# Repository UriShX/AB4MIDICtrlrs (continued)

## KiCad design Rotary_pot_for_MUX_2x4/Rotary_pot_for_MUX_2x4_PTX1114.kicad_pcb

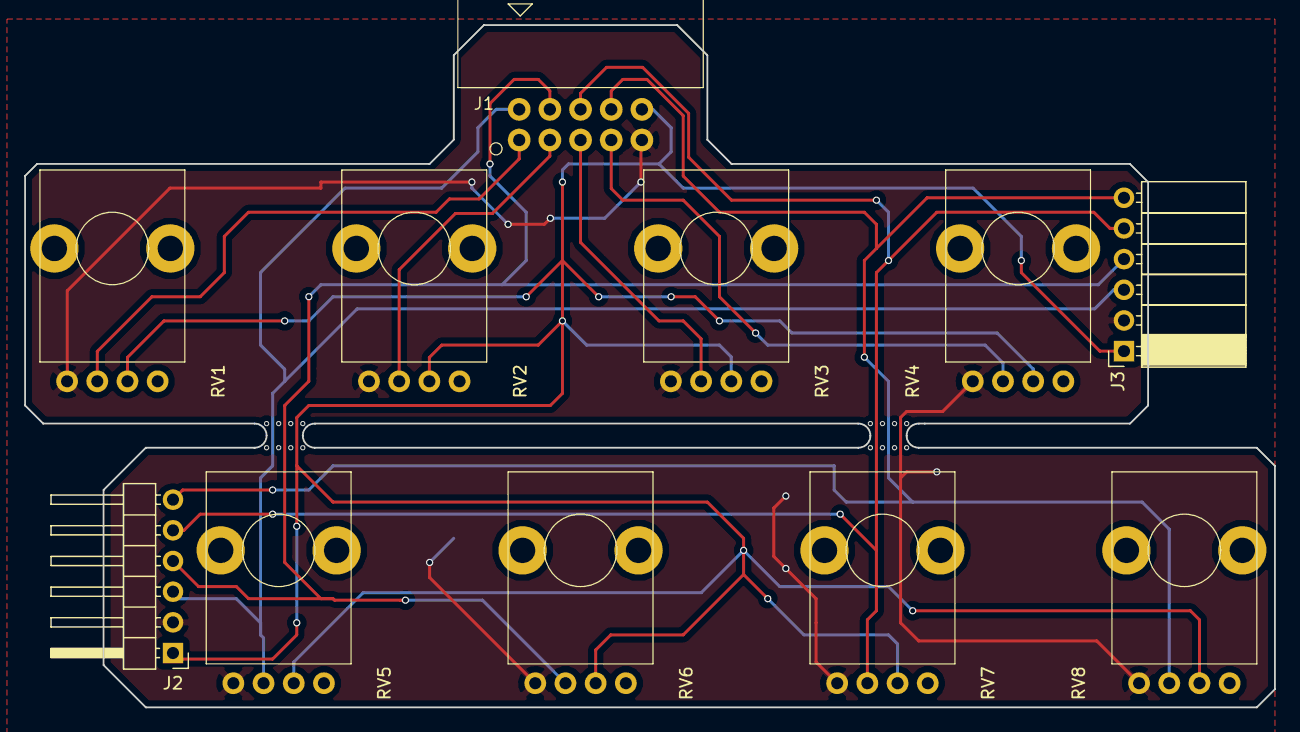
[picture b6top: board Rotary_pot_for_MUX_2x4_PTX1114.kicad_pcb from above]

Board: 2 copper layers, 103.5 x 56.5 mm, 11 parts (0 on the bottom side), 10 nets.

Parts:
J1: Conn_02x05_Odd_Even; 2X5-SHROUDED_rightAngle
J2: Conn_01x06_Male; Pin_Header_Angled_1x06_Pitch2.54mm
J3: Conn_01x06_Female; Socket_Strip_Angled_1x06_Pitch2.54mm
RV1, RV2, RV3, RV4, RV5, RV6, RV7, RV8: 10k_B; Potentiometer_Bourns_or_TT_PTV_PTT111-4_Horizontal

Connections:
GND: J1.9, J2.2, J3.2, RV1.1, RV2.1, RV3.1, RV4.1, RV5.1, RV6.1, RV7.1, RV8.1
unnamed: J1.1, RV1.2
unnamed: J1.2, J2.3, J3.3, RV5.2
unnamed: J1.3, RV2.2
unnamed: J1.4, J2.4, J3.4, RV6.2
unnamed: J1.5, RV3.2
unnamed: J1.6, J2.5, J3.5, RV7.2
unnamed: J1.7, RV4.2
unnamed: J1.8, J2.6, J3.6, RV8.2
VCC: J1.10, J2.1, J3.1, RV1.3, RV2.3, RV3.3, RV4.3, RV5.3, RV6.3, RV7.3, RV8.3

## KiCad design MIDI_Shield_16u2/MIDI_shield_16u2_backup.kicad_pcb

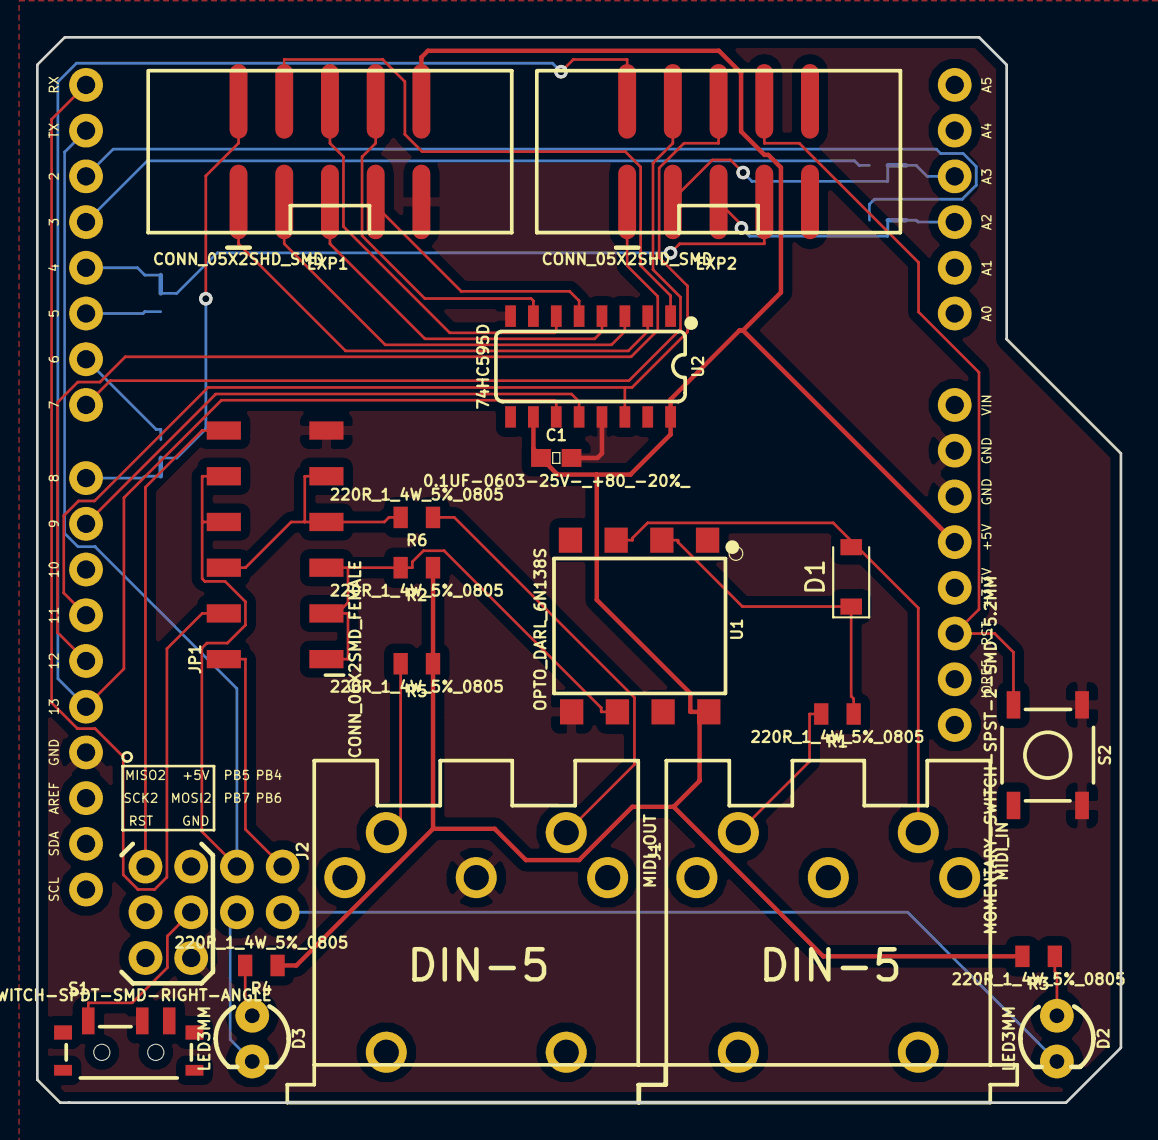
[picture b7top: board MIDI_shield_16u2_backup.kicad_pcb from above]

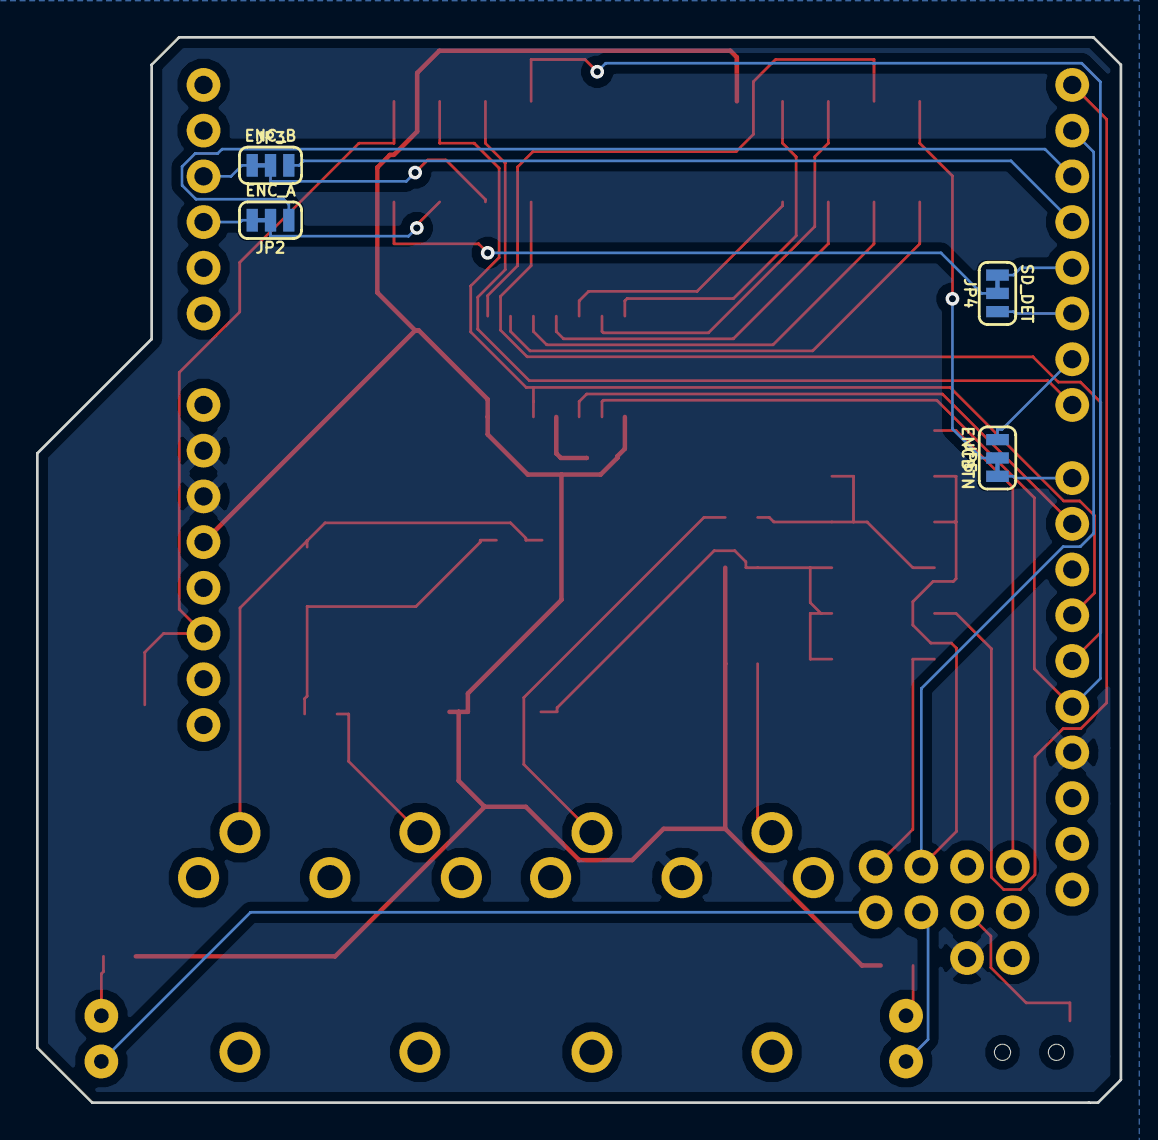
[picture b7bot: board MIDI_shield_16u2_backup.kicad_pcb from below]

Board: 2 copper layers, 60.2 x 59.2 mm, 24 parts (4 on the bottom side), 43 nets.

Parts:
B1: ARDUINO_UNO_R3_SHIELD_16u2_BREAKOUT; UNO_R3_SHIELD_16u2_BREAKOUT
C1: 0.1UF-0603-25V-_+80_-20%_; 0603
D1: 1N4148; D_SOD-123
D2, D3: LED3MM; LED_3MM
EXP1, EXP2: CONN_05X2SHD_SMD; 2X5-SHROUDED_SMD
J1: MIDI_IN; DIN5-RA-PTH
J2: MIDI_OUT; DIN5-RA-PTH
JP1: CONN_06X2SMD_FEMALE; 2X6_SMD
JP2: ENC_A; SMT-JUMPER_3_1-NC_TRACE_SILK
JP3: ENC_B; SMT-JUMPER_3_1-NC_TRACE_SILK
JP4: SD_DET; SMT-JUMPER_3_1-NC_TRACE_SILK
JP5: ENCBTN; SMT-JUMPER_3_1-NC_TRACE_SILK
R1, R2, R3, R4, R5, R6: 220R_1_4W_5%_0805; 0805
S1: SWITCH-SPDT-SMD-RIGHT-ANGLE; SWITCH_SPST_SMD_A
S2: MOMENTARY-SWITCH-SPST-2-SMD-5.2MM; TACTILE_SWITCH_SMD_5.2MM
U1: OPTO_DARL_6N138S; 8-SMD
U2: 74HC595D; SO16

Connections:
/16U2_RSTJP: B1.SI_2, S1.3
/16U2_RX: B1.PB4, JP1.2
/16U2_TX: B1.PB5, B1.TX, JP1.8, JP1.10
/328P_RX: B1.RX, JP1.4
/ARDUINO_RST: B1.RES, EXP2.8, S2.3, S2.4
/BUZZER: EXP1.1, U2.2
/ENC_A: EXP2.5, JP2.2
/ENC_A_NC: B1.A2, JP2.3
/ENC_A_NO: B1.D2, JP2.1
/ENC_B: EXP2.3, JP3.2
/ENC_BTN: EXP1.2, JP5.2
/ENC_BTN_NC: B1.D8, JP5.3
/ENC_BTN_NO: B1.D6, JP5.1
/ENC_B_NC: B1.A3, JP3.3
/ENC_B_NO: B1.D3, JP3.1
/FAST_SERIAL: B1.SO_2, JP1.12
/LCD4: EXP1.5, U2.4
/LCD5: EXP1.6, U2.6
/LCD6: EXP1.7, U2.5
/LCD7: EXP1.8, U2.7
/LCD&BUZZER_CS: B1.D9, U2.12
/LCDE: EXP1.3, U2.3
/LCDRS: EXP1.4, U2.1
/MIDI_IN: JP1.1, JP1.3, JP1.5, R2.1, U1.6
/MIDI_OUT: JP1.6, JP1.7, JP1.9, R6.2
/MISO_: B1.D12, EXP2.1
/MOSI_: B1.D11, EXP2.6, U2.14
/SCK_: B1.D13, EXP2.2, U2.11
/SD_CS: B1.D7, EXP2.4
/SD_DET: EXP2.7, JP4.2
/SD_DET_NC: B1.D4, JP4.3
/SD_DET_NO: B1.D5, JP4.1
/STATUS_LED1: B1.PB6, D2.K
/STATUS_LED2: B1.PB7, D3.K
GND: B1.GND2, B1.GND@, C1.2, EXP1.9, J2.2, JP1.11, S1.2, S2.1, S2.2, U1.5, U2.8, U2.13
unnamed: D1.1, R1.2, U1.2
unnamed: D1.2, J1.4, U1.3
unnamed: D2.A, R3.2
unnamed: D3.A, R4.2
unnamed: J1.5, R1.1
unnamed: J2.4, R6.1
unnamed: J2.5, R5.1
VCC: B1.5V, C1.1, EXP1.10, R2.2, R3.1, R4.1, R5.2, U1.8, U2.10, U2.16

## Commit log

2020-02-05 add buttons and pots sub-boards, push changes
